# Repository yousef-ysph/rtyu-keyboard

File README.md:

# RTYU - RP2040 based split keyboard

RTYU is a 54 custom split ortho-linear keyboard inspired by [silakka54](https://github.com/Squalius-cephalus/silakka54).
RTYU uses hot-swap sockets for low profile choc v2 or cherry mx keyswitches (depending on the pcb)

Firmware is based on [QMK](https://github.com/qmk/qmk_firmware) and there is a [Vial](https://github.com/vial-kb/vial-qmk) port for Vial GUI app

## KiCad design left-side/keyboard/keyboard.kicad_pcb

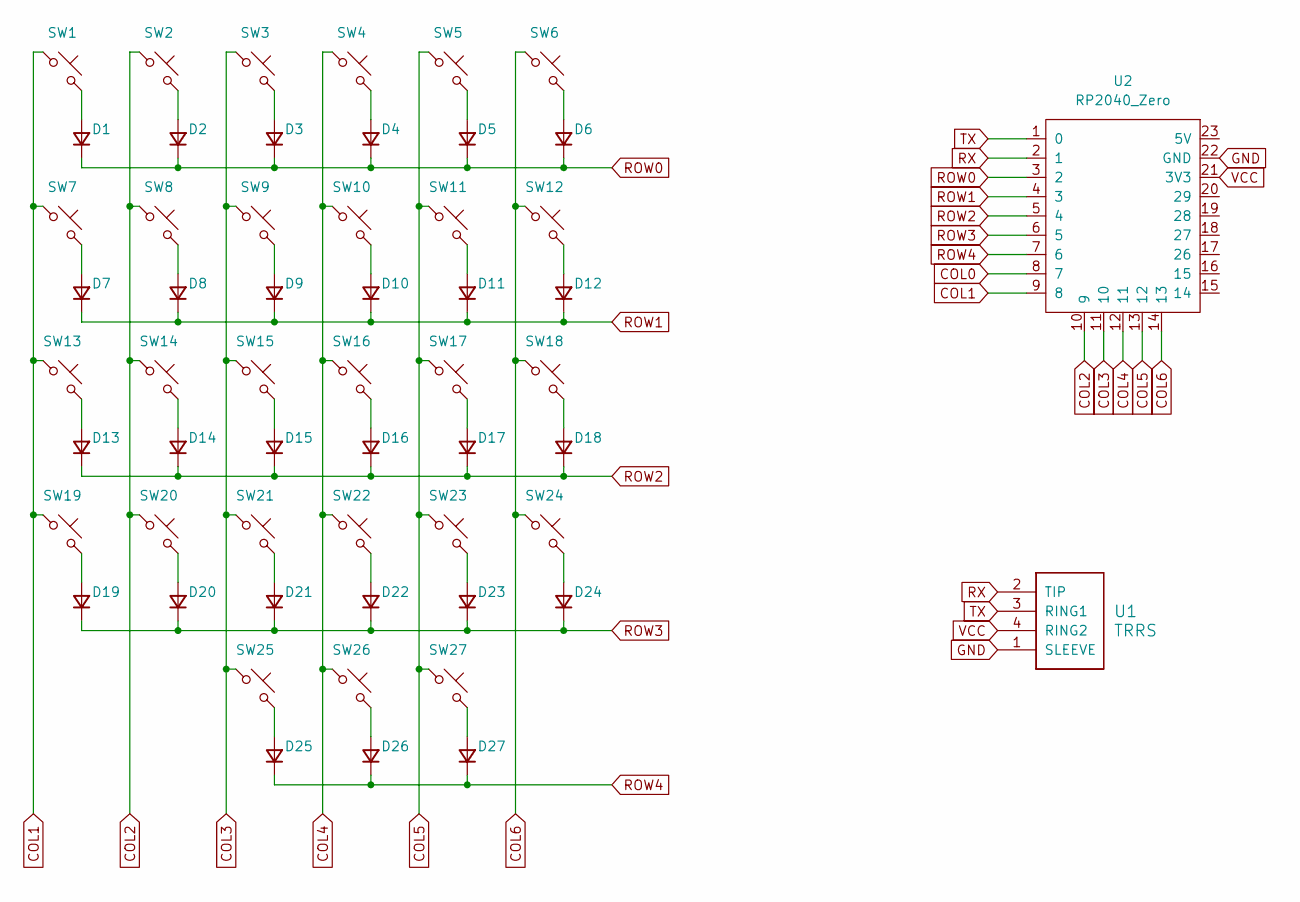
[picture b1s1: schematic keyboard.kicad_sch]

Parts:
D1, D2, D3, D4, D5, D6, D7, D8, D9, D10, D11, D12, D13, D14, D15, D16, D17, D18, D19, D20, D21, D22, D23, D24, D25, D26, D27: D; D_SOD-123F
SW1, SW2, SW3, SW4, SW5, SW6, SW7, SW8, SW9, SW10, SW11, SW12, SW13, SW14, SW15, SW16, SW17, SW18, SW19, SW20, SW21, SW22, SW23, SW24, SW25, SW26, SW27: SW_Push; SW_Hotswap_Kailh_Choc_V2_1.00u
U1: TRRS; TRRS_PJ-320A
U2: RP2040_Zero

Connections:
COL0: U2.8 (7)
COL1: SW1.1, SW7.1, SW13.1, SW19.1, U2.9 (8)
COL2: SW2.1, SW8.1, SW14.1, SW20.1, U2.10 (9)
COL3: SW3.1, SW9.1, SW15.1, SW21.1, SW25.1, U2.11 (10)
COL4: SW4.1, SW10.1, SW16.1, SW22.1, SW26.1, U2.12 (11)
COL5: SW5.1, SW11.1, SW17.1, SW23.1, SW27.1, U2.13 (12)
COL6: SW6.1, SW12.1, SW18.1, SW24.1, U2.14 (13)
GND: U1.1 (SLEEVE), U2.22 (GND)
unnamed: D1.2 (A), SW1.2
unnamed: D2.2 (A), SW2.2
unnamed: D3.2 (A), SW3.2
unnamed: D4.2 (A), SW4.2
unnamed: D5.2 (A), SW5.2
unnamed: D6.2 (A), SW6.2
unnamed: D7.2 (A), SW7.2
unnamed: D8.2 (A), SW8.2
unnamed: D9.2 (A), SW9.2
unnamed: D10.2 (A), SW10.2
unnamed: D11.2 (A), SW11.2
unnamed: D12.2 (A), SW12.2
unnamed: D13.2 (A), SW13.2
unnamed: D14.2 (A), SW14.2
unnamed: D15.2 (A), SW15.2
unnamed: D16.2 (A), SW16.2
unnamed: D17.2 (A), SW17.2
unnamed: D18.2 (A), SW18.2
unnamed: D19.2 (A), SW19.2
unnamed: D20.2 (A), SW20.2
unnamed: D21.2 (A), SW21.2
unnamed: D22.2 (A), SW22.2
unnamed: D23.2 (A), SW23.2
unnamed: D24.2 (A), SW24.2
unnamed: D25.2 (A), SW25.2
unnamed: D26.2 (A), SW26.2
unnamed: D27.2 (A), SW27.2
ROW0: D1.1 (K), D2.1 (K), D3.1 (K), D4.1 (K), D5.1 (K), D6.1 (K), U2.3 (2)
ROW1: D7.1 (K), D8.1 (K), D9.1 (K), D10.1 (K), D11.1 (K), D12.1 (K), U2.4 (3)
ROW2: D13.1 (K), D14.1 (K), D15.1 (K), D16.1 (K), D17.1 (K), D18.1 (K), U2.5 (4)
ROW3: D19.1 (K), D20.1 (K), D21.1 (K), D22.1 (K), D23.1 (K), D24.1 (K), U2.6 (5)
ROW4: D25.1 (K), D26.1 (K), D27.1 (K), U2.7 (6)
RX: U1.2 (TIP), U2.2 (1)
TX: U1.3 (RING1), U2.1 (0)
VCC: U1.4 (RING2), U2.21 (3V3)

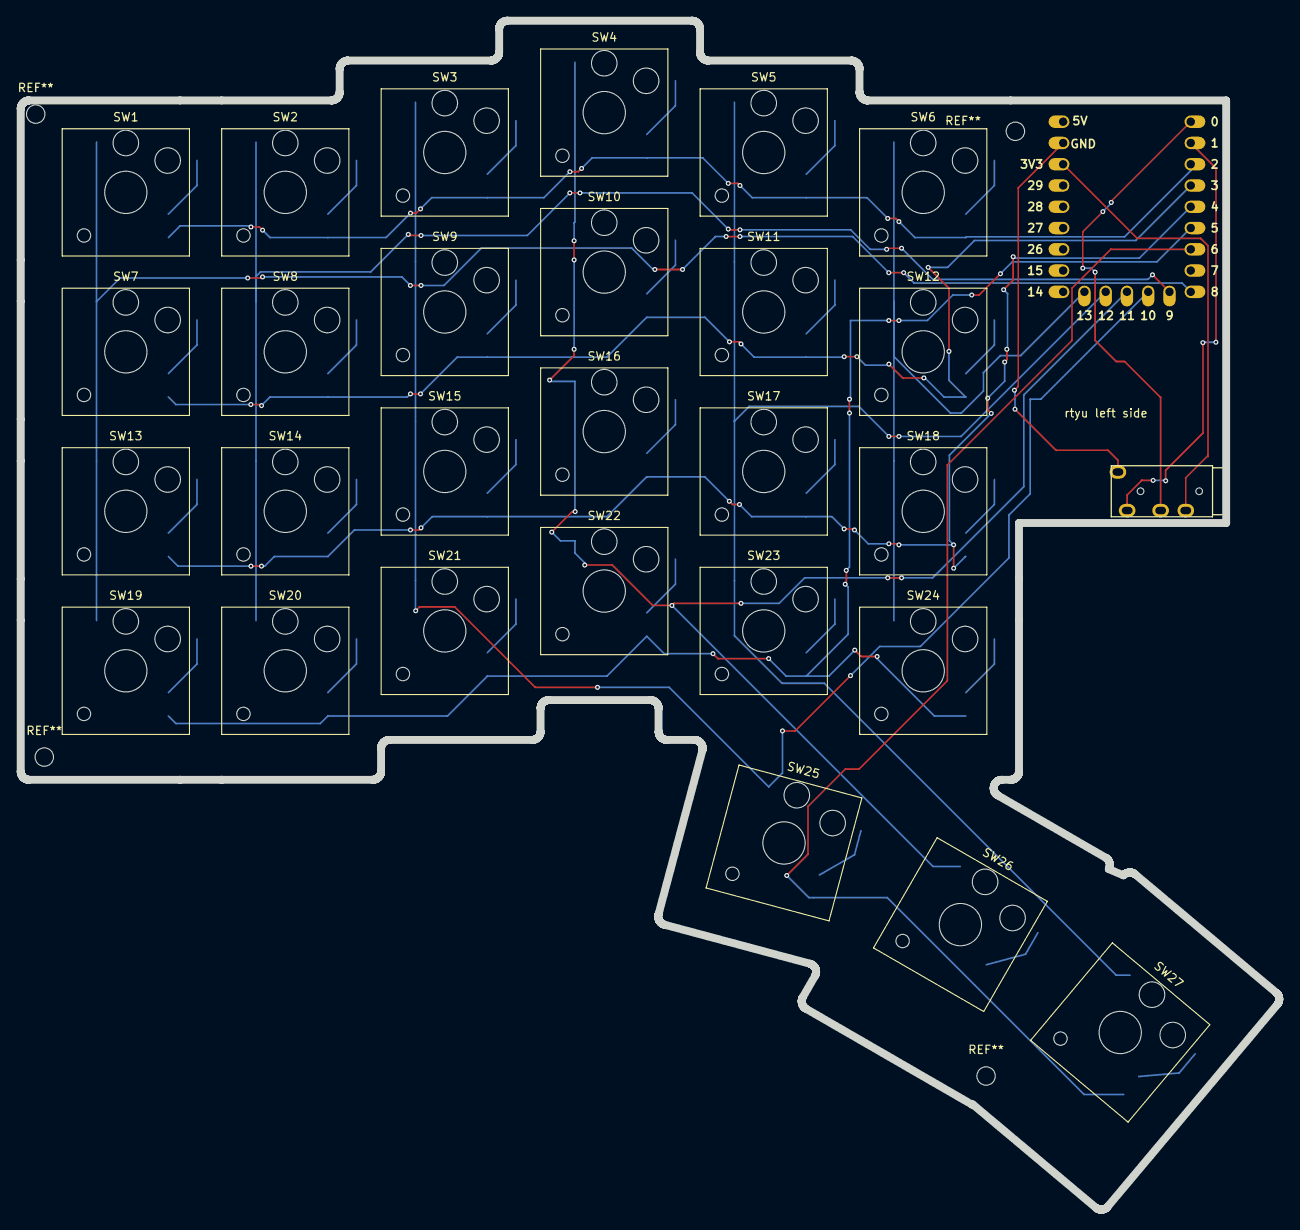
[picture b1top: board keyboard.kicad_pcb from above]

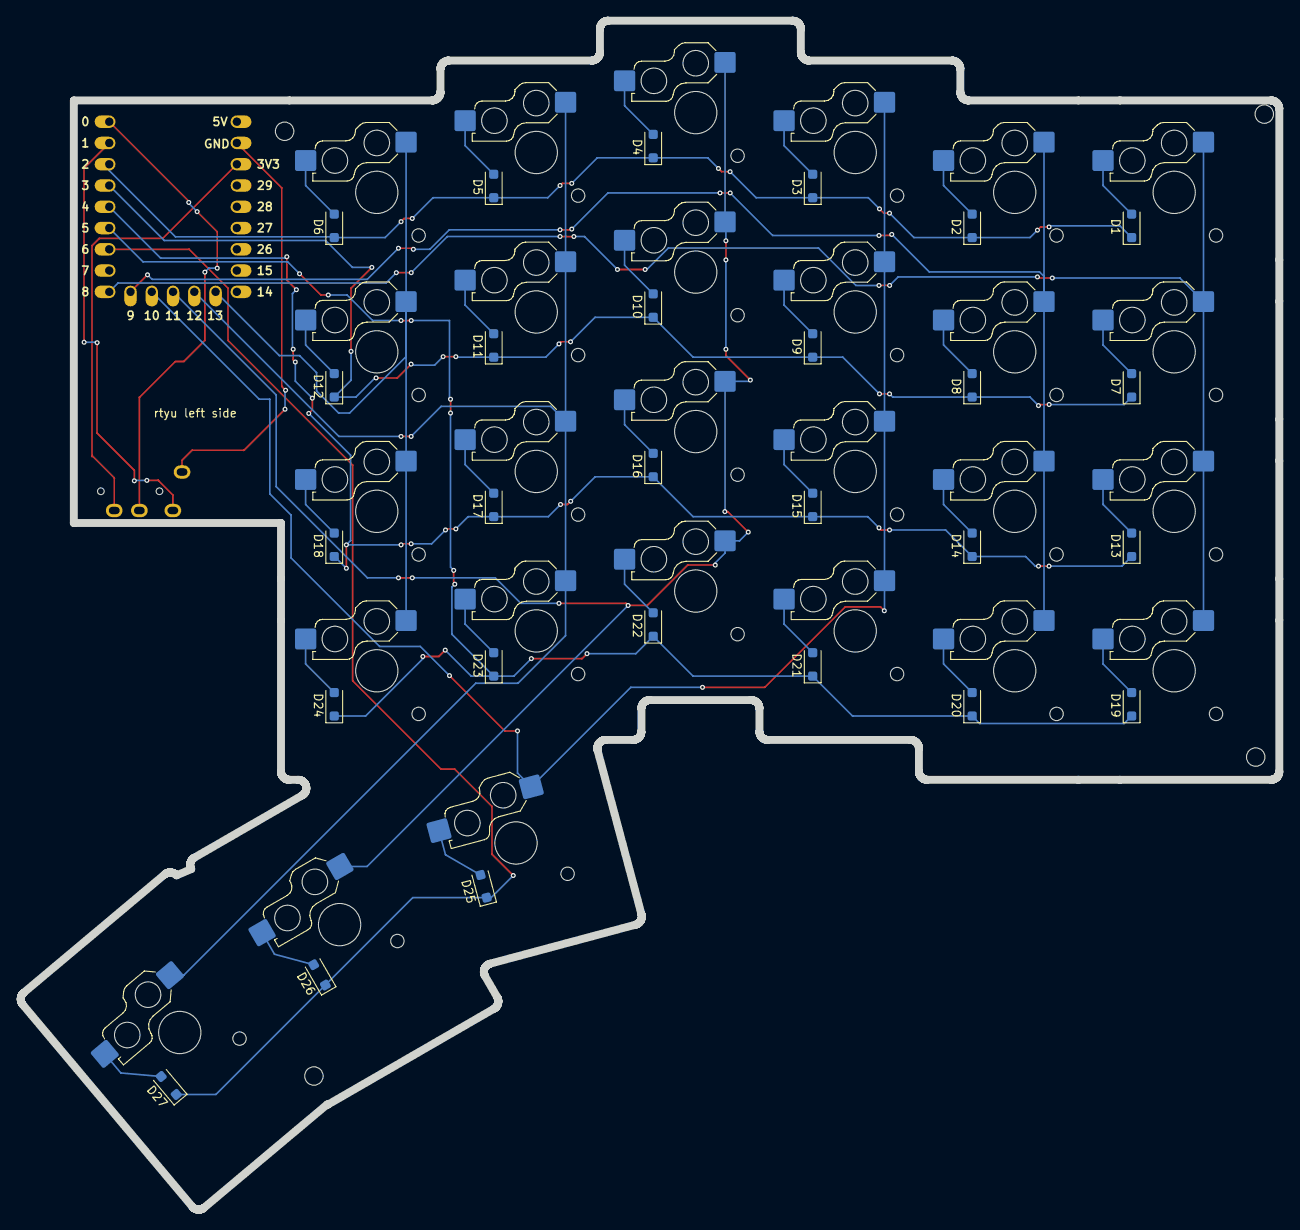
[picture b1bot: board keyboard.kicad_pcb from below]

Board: 2 copper layers, 150.3 x 142.0 mm, 56 parts (27 on the bottom side), 42 nets.
